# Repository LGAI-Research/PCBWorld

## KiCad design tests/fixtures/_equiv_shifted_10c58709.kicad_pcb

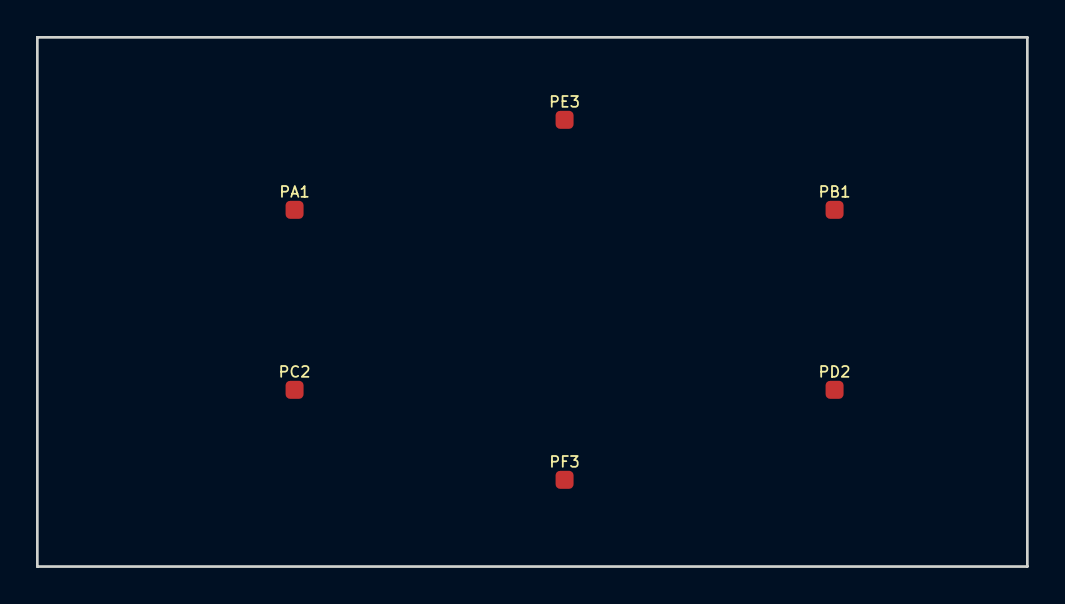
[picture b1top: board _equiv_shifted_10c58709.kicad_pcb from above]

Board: 2 copper layers, 55.0 x 29.4 mm, 6 parts (0 on the bottom side), 3 nets, no tracks yet.

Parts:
PA1: Pad1; FCu
PB1: Pad1; FCu
PC2: Pad2; FCu
PD2: Pad2; FCu
PE3: Pad3; FCu
PF3: Pad3; FCu

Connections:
NET1: PA1.1, PB1.1
NET2: PC2.1, PD2.1
NET3: PE3.1, PF3.1

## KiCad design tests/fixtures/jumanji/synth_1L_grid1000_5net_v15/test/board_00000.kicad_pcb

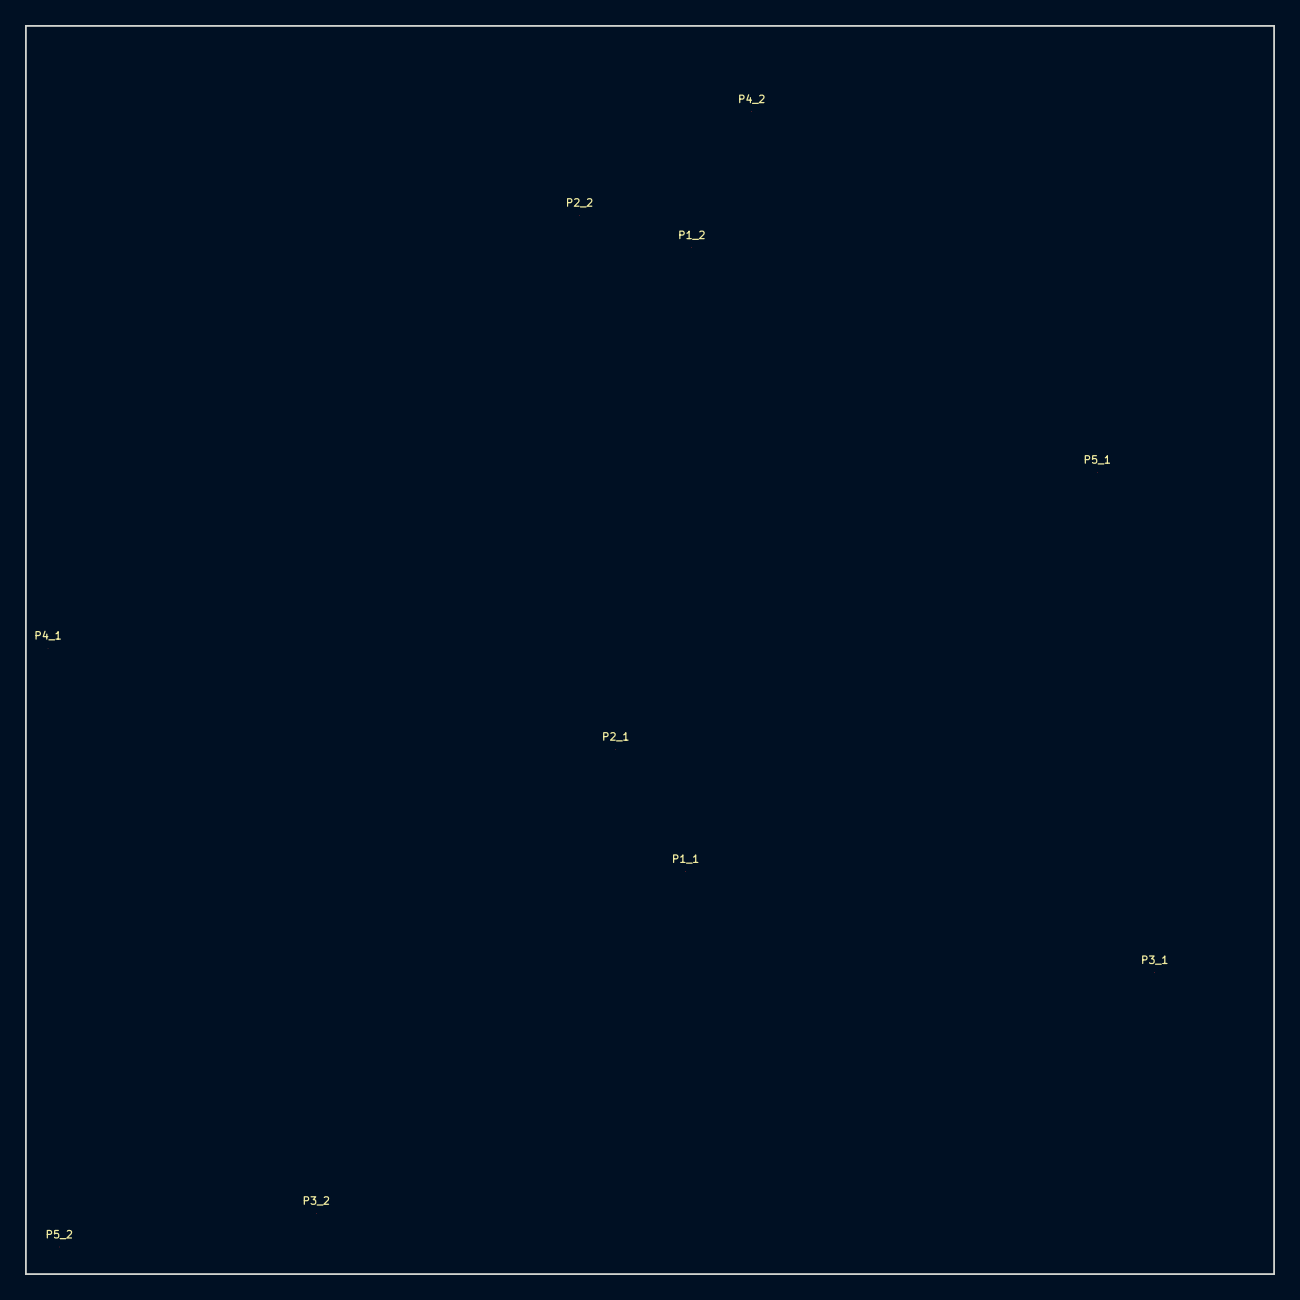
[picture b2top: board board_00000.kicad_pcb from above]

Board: 2 copper layers, 100.0 x 100.0 mm, 10 parts (0 on the bottom side), 5 nets, no tracks yet.

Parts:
P1_1, P2_1, P3_1, P4_1, P5_1: Pad1; FCu
P1_2, P2_2, P3_2, P4_2, P5_2: Pad2; FCu

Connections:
NET1: P1_1.1, P1_2.1
NET2: P2_1.1, P2_2.1
NET3: P3_1.1, P3_2.1
NET4: P4_1.1, P4_2.1
NET5: P5_1.1, P5_2.1
